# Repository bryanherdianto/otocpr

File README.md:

<h1 align="center">OtoCPR (Auto-CPR for Infants)</h1>

<p align="center">
  Adaptive infant mechanical chest compression system with dual-feedback control and live telemetry.
</p>

## Table of Contents

- [Overview](#overview)
- [Clinical Background and Problem Statement](#clinical-background-and-problem-statement)
- [System Architecture](#system-architecture)
  - [Dual-Feedback Control](#dual-feedback-control)
- [Hardware and PCB Design](#hardware-and-pcb-design)
  - [Custom PCB Details](#custom-pcb-details)
  - [3D Board View](#3d-board-view)
  - [Pin Mapping](#pin-mapping)
- [Firmware (ESP32)](#firmware-esp32)
  - [GPS Simulation](#gps-simulation)
  - [Build Environments](#build-environments)
- [Flutter Companion App](#flutter-companion-app)
- [Project Structure](#project-structure)
- [Quick Start](#quick-start)
  - [1. Firmware and Wokwi](#1-firmware-and-wokwi)
  - [2. Flutter App](#2-flutter-app)
- [Team](#team)

## Overview

OtoCPR is a portable mechanical chest compression device made for infants under 1 year old during CPR. It was developed at the Department of Electrical Engineering, Universitas Indonesia (FTUI), with pediatric intensive care specialists from FKUI-RSCM to reduce rescuer fatigue and keep compressions steady.

The system includes:

1. ESP32 motor control running on FreeRTOS.
2. Dual sensor feedback using a rotary encoder for depth and an HX711 load cell for force limits.
3. A custom 2-layer PCB with a 24V-to-5V buck regulator, level shifters, and motor driver wiring.
4. Wireless Bluetooth (BLE) and GPS data streamed to a Flutter app.

## Clinical Background and Problem Statement

Pediatric CPR guidelines from the American Heart Association (AHA) and European Resuscitation Council (ERC) recommend:

- Rate: 100 to 120 compressions per minute (CPM).
- Depth: about one-third of chest depth (roughly 3.5 to 4.0 cm).
- Recoil: full chest release between compressions.

<p align="center">
  
  <br />
  Figure 1: Adult mechanical CPR systems (left) compared with manual two-finger infant CPR (right).
</p>

Why OtoCPR is needed:

- Adult CPR machines (such as LUCAS 3) push 5.0 to 5.5 cm with over 300 N of force, which is unsafe for infants.
- Manual infant CPR causes hand fatigue within about 2 minutes, making depth and rate drop.
- Dedicated automated CPR devices for infants are rare, especially for ambulance transport and rural clinics.

## System Architecture

### Dual-Feedback Control

OtoCPR uses two sensors to keep compressions accurate and safe:

1. Depth control (Rotary Encoder):
   - A 600 PPR quadrature encoder (2400 counts per turn) tracks travel down to about 0.0033 mm per step.
   - A PID loop adjusts motor PWM output to hold the target stroke (3.5 to 4.0 cm) and speed (100 to 120 CPM).

2. Force limit (HX711 Load Cell):
   - A 24-bit load cell reads compression force continuously.
   - If force gets too high, the controller slows the motor and allows full recoil.

```mermaid
flowchart LR
    SP[AHA Target 100-120 CPM] --> PID[ESP32 PID]
    PID --> Driver[Motor Driver]
    Driver --> Actuator[DC Actuator]
    Actuator --> Chest[Infant Manikin]
    Actuator -. Depth .-> Enc[Rotary Encoder]
    Chest -. Force .-> LC[HX711 Load Cell]
    Enc -- Depth Feedback --> PID
    LC -- Force Limit --> PID
    PID -- BLE / Serial --> App[Flutter App]
```

## Hardware and PCB Design

The electronics sit on a custom 2-layer KiCad PCB to avoid loose breadboard wires and cut electrical noise.

### Custom PCB Details

<p align="center">
  
  <br />
  Figure 2: 2D KiCad board layout and specifications (DESPRO 2026 Kelompok 20).
</p>

| Item                | Value                            | Notes                                           |
| :------------------ | :------------------------------- | :---------------------------------------------- |
| Board Size          | 60.00 mm x 100.00 mm             | Compact size for portable housing               |
| Layers              | 2 copper layers (top and bottom) | 1 oz copper (0.035 mm)                          |
| Material            | FR4, 1.51 mm core                | Total thickness 1.60 mm                         |
| Min Track / Spacing | 0.200 mm / 0.200 mm              | Wider traces for motor power                    |
| Min Hole Size       | 0.400 mm                         | Plated through-holes                            |
| Power Converter     | XL4015E1 DC-DC buck              | Steps 24V battery down to 5V (5A peak)          |
| Level Shifter       | Dual BSS138 N-MOSFET             | Converts 5V encoder signals to 3.3V             |
| Protection          | 3A glass fuse and SS34 diodes    | Surge, reverse polarity, and flyback protection |

### 3D Board View

<p align="center">
  
  <br />
  Figure 3: 3D render of the assembled control board.
</p>

### Pin Mapping

| Part                 | Module Pin      | ESP32 Pin           | Notes                                |
| :------------------- | :-------------- | :------------------ | :----------------------------------- |
| Main Power           | Buck Output     | 5V / GND            | 5V rail from XL4015 converter        |
| Logic Reference      | 3.3V Rail       | 3V3                 | Reference for level shifter and MCU  |
| Rotary Encoder ChA   | Output A        | GPIO 32 (or GPIO 2) | Pulse interrupt via level shifter    |
| Rotary Encoder ChB   | Output B        | GPIO 33 (or GPIO 3) | Direction signal via level shifter   |
| HX711 Load Cell      | DT / SCK        | GPIO 19 / GPIO 18   | Weight sensor data and clock         |
| Motor Driver PWM     | IN1 / IN2       | GPIO 25 / GPIO 26   | 5 kHz, 8-bit PWM speed and direction |
| Driver Enable        | EN              | GPIO 27             | Motor enable (active HIGH)           |
| I2C Display          | SDA / SCL       | GPIO 21 / GPIO 22   | Status LCD (0x27 or 0x3C)            |
| NEO-6M GPS           | TX / RX         | GPIO 16 / GPIO 17   | Serial2 at 9600 baud                 |
| Buzzer / Stop Button | Buzzer / Switch | GPIO 8              | Emergency alarm and manual stop      |

## Firmware (ESP32)

Built with PlatformIO and C++, the firmware splits motor control and data sending across both ESP32 cores. See [Firmware/README.md](./Firmware/README.md) for full firmware instructions.

- Core 1 (Motor Control):
  - Counts encoder pulses using hardware interrupts.
  - Runs the PID loop every 10 ms (100 Hz) with deadband handling.
- Core 0 (Sensors and Data):
  - Reads the HX711 load cell and NEO-6M GPS.
  - Sends a 14-column CSV line every 200 ms (5 Hz) over Bluetooth (BLE) and USB Serial (115200 baud).

CSV format:

```text
Time(ms),Set_RPM,Actual_RPM,PWM,Raw_Counts,Freq_Hz,LoadCell,GPS_Fix,Latitude,Longitude,Satellites,Speed_kmh,Altitude_m,GPS_UTC
```

### GPS Simulation

To test GPS without a physical module or outdoor signal:

- A built-in GPS emulator generates NMEA data inside the ESP32.
- A custom Wokwi GPS chip (Firmware/chips/gps-neo6m.chip.c) adds live sliders for speed, heading, satellites, and signal strength.

### Build Environments

```bash
# Standard build for real hardware or Wokwi
pio run -e esp32doit-devkit-v1

# Built-in GPS software simulator
pio run -e esp32doit-devkit-v1-gps-sim -t upload

# Wireless Bluetooth (BLE) telemetry build
pio run -e esp32doit-devkit-v1-ble -t upload

# Desktop GPS tests
pio test -e native
```

## Flutter Companion App

The Flutter app runs on Android, iOS, Windows, macOS, and Linux:

- System Monitor: live gauges and charts for target vs actual rate, depth, PWM, and force.
- GPS Tracker: live unit location during transport.
- Edge AI Diagnostics: uses a Gemma model pipeline to flag anomalies, overheating risk, and compression consistency.
- Two Connection Modes:
  1. Bluetooth (BLE): connects wirelessly to OtoCPR Unit 01.
  2. Wokwi TCP: connects to the local simulator on 127.0.0.1:4000 (or 10.0.2.2:4000 on Android Emulator).

## Project Structure

```text
otocpr-main/
├── README.md                  Project overview
├── Hardware/                  Schematics, BOM, and datasheets
│   ├── BOM.md                 Parts list
│   ├── Datasheet/             Component datasheets
│   └── Schematic/             KiCad files
├── Firmware/                  PlatformIO ESP32 firmware
│   ├── platformio.ini         Build environments and libraries
│   ├── diagram.json           Wokwi circuit wiring
│   ├── wokwi.toml             Wokwi config
│   ├── log_serial.py          CSV logger script
│   ├── src/                   Firmware source code
│   ├── lib/                   GPS parser and helper code
│   └── chips/                 Custom Wokwi GPS chip
├── docs/                      Reports and figures
├── lib/                       Flutter app source code
│   ├── main.dart              App entry point
│   ├── models/                Telemetry data models
│   ├── screens/               App pages
│   ├── services/              BLE and Wokwi connection handlers
│   └── widgets/               Charts, gauges, and cards
└── assets/                    Images and icons
```

## Quick Start

### 1. Firmware and Wokwi

1. Install VS Code with the PlatformIO IDE and Wokwi for VS Code extensions.
2. Open the Firmware folder in VS Code.
3. Build the firmware:
   ```bash
   pio run -e esp32doit-devkit-v1
   ```
4. Open Firmware/diagram.json and click Start Simulation (opens local port 4000).

### 2. Flutter App

1. Install Flutter (3.0 or newer).
2. Install packages:
   ```bash
   flutter pub get
   ```
3. Run the app:
   ```bash
   flutter run -d macos
   flutter run -d windows
   flutter run -d android
   ```
4. In the Robotic System card, open the menu and select Connect Wokwi Simulator (:4000), or scan for OtoCPR Unit 01 over Bluetooth.

## Team

- Raditya Danendra - Project Lead, Control and Embedded System
- Bryan Herdianto - Flutter App and Telemetry Pipeline
- Daffa Sayra Firdaus - Sensor Instrumentation and Edge AI
- Fathih Rayyandra Firmansyah - Power Management and Electronics
- Lukas Sudibyo Putra Parulian - Mechanical Design and Actuation

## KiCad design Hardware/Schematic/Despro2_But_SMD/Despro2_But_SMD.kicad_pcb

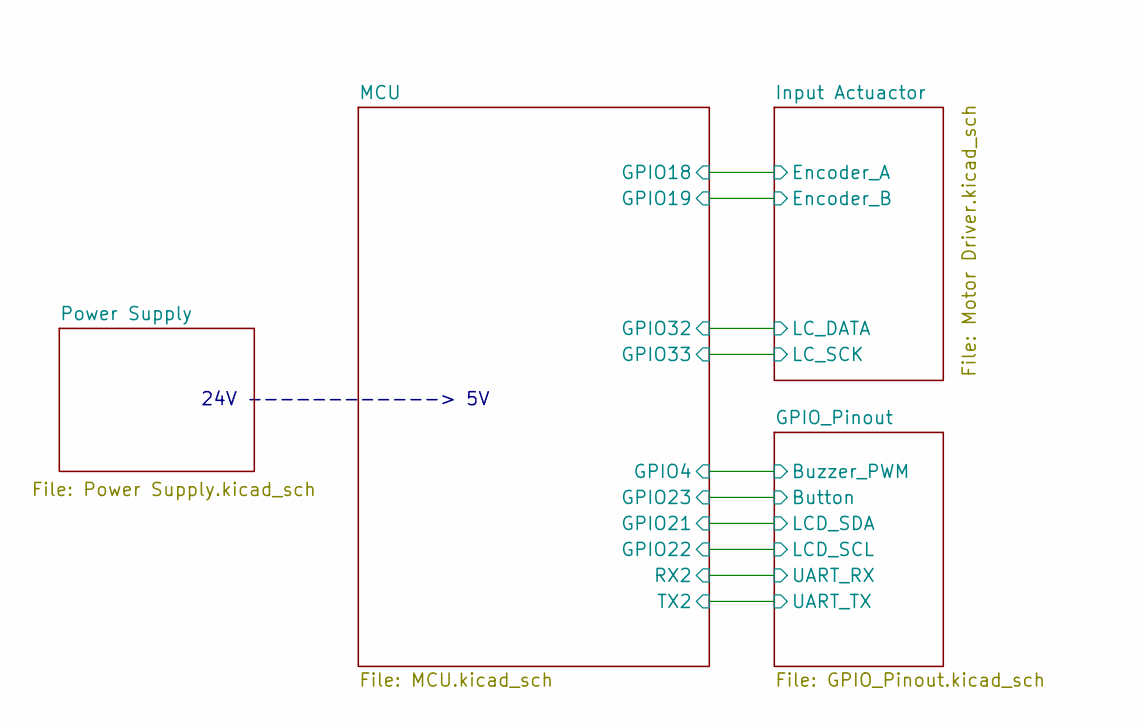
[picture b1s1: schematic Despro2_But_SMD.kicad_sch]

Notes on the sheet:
24V ------------> 5V

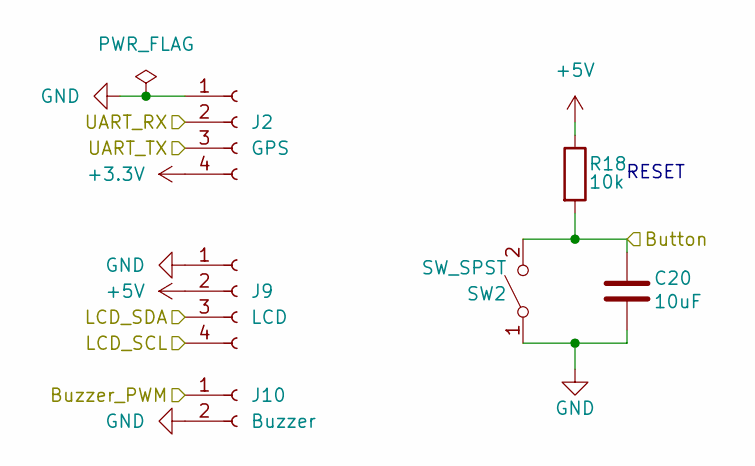
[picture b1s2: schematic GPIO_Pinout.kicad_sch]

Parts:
C20: 10uF; C_1206_3216Metric_Pad1.33x1.80mm_HandSolder; MANUFACTURER_PART_NUMBER GRM188D71A106KA73D
J2: GPS; Molex_KK-254_AE-6410-04A_1x04_P2.54mm_Vertical
J9: LCD; Molex_KK-254_AE-6410-04A_1x04_P2.54mm_Vertical
J10: Buzzer; Molex_KK-254_AE-6410-02A_1x02_P2.54mm_Vertical
R18: 10k; R_1206_3216Metric_Pad1.30x1.75mm_HandSolder; MANUFACTURER_PART_NUMBER RT0603FRE0710KL
SW2: SW_SPST; SW_PUSH_6mm; MANUFACTURER_PART_NUMBER TL1105F160QWITHSTRAIGHT

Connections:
+3.3V: J2.4; also elsewhere on the board
+5V: J9.2, R18.1; also elsewhere on the board
/MCU/GPIO4: J10.1; also elsewhere on the board
/MCU/GPIO21: J9.3; also elsewhere on the board
/MCU/GPIO22: J9.4; also elsewhere on the board
/MCU/GPIO23: C20.1, R18.2, SW2.2 (B); also elsewhere on the board
/MCU/RX2: J2.2; also elsewhere on the board
/MCU/TX2: J2.3; also elsewhere on the board
GND: C20.2, J2.1, J9.1, J10.2, SW2.1 (A); also elsewhere on the board

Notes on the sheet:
RESET

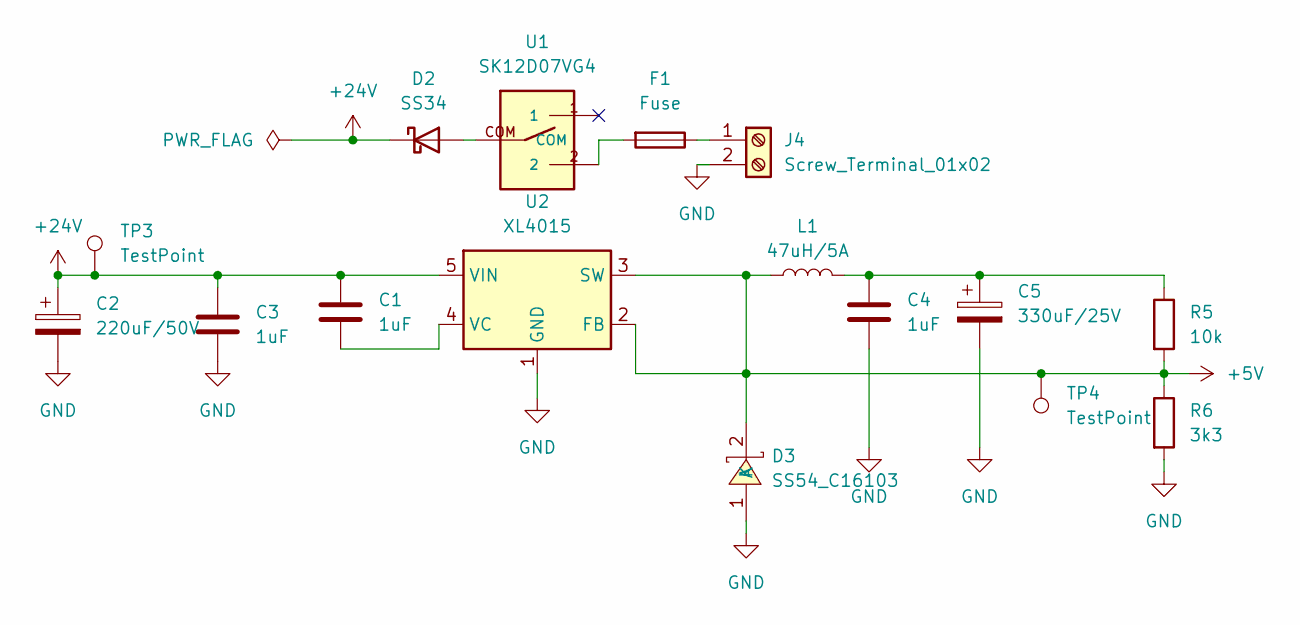
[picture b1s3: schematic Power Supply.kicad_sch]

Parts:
C1, C3, C4: 1uF; C_1206_3216Metric_Pad1.33x1.80mm_HandSolder
C2: 220uF/50V; CP_Radial_D10.0mm_P5.00mm
C5: 330uF/25V; CP_Radial_D8.0mm_P3.50mm
D2: SS34; D_SMA
D3: SS54_C16103; SMC_L7.1-W6.2-LS8.1-R-RD; MPN SS54C; LCSC Part C16103
F1: Fuse; Fuseholder_Littelfuse_Nano2_154x
J4: Screw_Terminal_01x02; TerminalBlock_Phoenix_PT-1,5-2-3.5-H_1x02_P3.50mm_Horizontal
L1: 47uH/5A; L_Sunlord_MWSA1206S-1R5
R5: 10k; R_1206_3216Metric_Pad1.30x1.75mm_HandSolder
R6: 3k3; R_1206_3216Metric_Pad1.30x1.75mm_HandSolder
TP3, TP4: TestPoint; PinHeader_1x01_P2.54mm_Vertical
U1: SK12D07VG4
U2: XL4015; TO-263-5_TabPin3

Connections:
+5V: D3.2 (K), L1.1, R5.2, R6.1, TP4.1 (1_1), U2.2 (FB), U2.3 (SW); also elsewhere on the board
+24V: C1.1, C2.1, C3.1, D2.1 (K), TP3.1 (1_1), U2.5 (VIN)
GND: C2.2, C3.2, C4.2, C5.2, D3.1 (A), J4.2, R6.2, U1.M1, U1.M2, U2.1 (GND); also elsewhere on the board
unnamed: C4.1, C5.1, L1.2, R5.1
unnamed: D2.2 (A), U1.COM
unnamed: F1.2, U1.2
unnamed: F1.1, J4.1
unnamed: C1.2, U2.4 (VC)

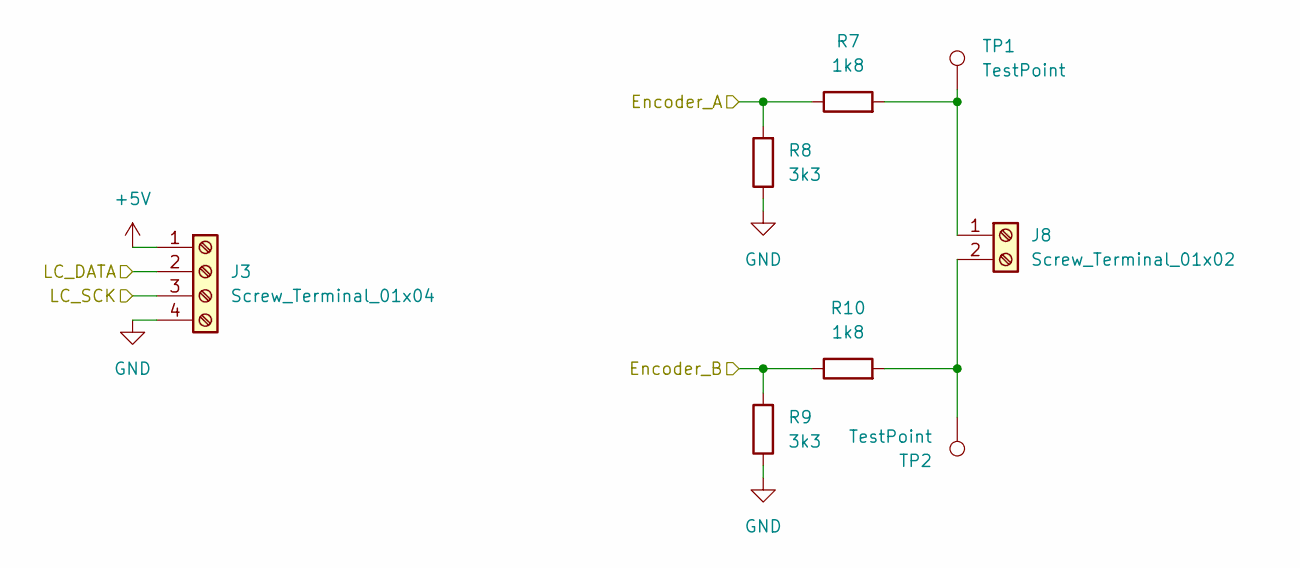
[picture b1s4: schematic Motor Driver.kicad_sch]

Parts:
J3: Screw_Terminal_01x04; TerminalBlock_Phoenix_PT-1,5-4-3.5-H_1x04_P3.50mm_Horizontal
J8: Screw_Terminal_01x02; TerminalBlock_Phoenix_PT-1,5-2-3.5-H_1x02_P3.50mm_Horizontal
R7, R10: 1k8; R_1206_3216Metric_Pad1.30x1.75mm_HandSolder
R8, R9: 3k3; R_1206_3216Metric_Pad1.30x1.75mm_HandSolder
TP1, TP2: TestPoint; PinHeader_1x01_P2.54mm_Vertical

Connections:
+5V: J3.1; also elsewhere on the board
/MCU/GPIO18: R7.1, R8.2; also elsewhere on the board
/MCU/GPIO19: R9.2, R10.1; also elsewhere on the board
/MCU/GPIO32: J3.2; also elsewhere on the board
/MCU/GPIO33: J3.3; also elsewhere on the board
GND: J3.4, R8.1, R9.1; also elsewhere on the board
unnamed: J8.1, R7.2, TP1.1 (1_1)
unnamed: J8.2, R10.2, TP2.1 (1_1)

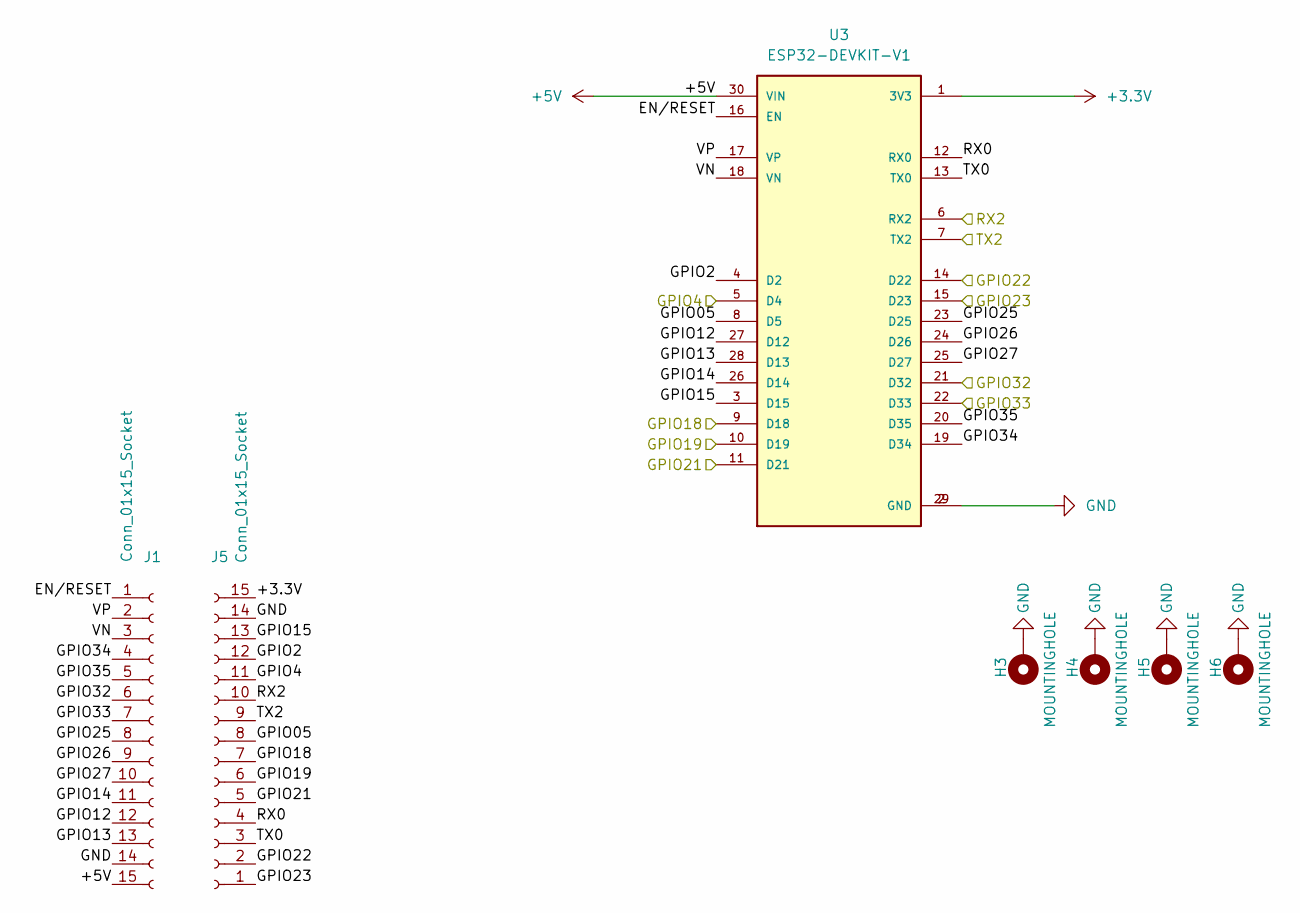
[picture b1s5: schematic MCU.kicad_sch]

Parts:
H3, H4, H5, H6: MOUNTINGHOLE; MountingHole_3.2mm_M3_Pad_Via
J1, J5: Conn_01x15_Socket; PinSocket_1x15_P2.54mm_Vertical
U3: ESP32-DEVKIT-V1; MODULE_ESP32_DEVKIT_V1; PARTREV N/A

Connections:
+3.3V: J5.15, U3.1 (3V3); also elsewhere on the board
+5V: J1.15, U3.30 (VIN); also elsewhere on the board
/MCU/EN/RESET: J1.1, U3.16 (EN)
/MCU/GPIO2: J5.12, U3.4 (D2)
/MCU/GPIO4: J5.11, U3.5 (D4); also elsewhere on the board
/MCU/GPIO05: J5.8, U3.8 (D5)
/MCU/GPIO12: J1.12, U3.27 (D12)
/MCU/GPIO13: J1.13, U3.28 (D13)
/MCU/GPIO14: J1.11, U3.26 (D14)
/MCU/GPIO15: J5.13, U3.3 (D15)
/MCU/GPIO18: J5.7, U3.9 (D18); also elsewhere on the board
/MCU/GPIO19: J5.6, U3.10 (D19); also elsewhere on the board
/MCU/GPIO21: J5.5, U3.11 (D21); also elsewhere on the board
/MCU/GPIO22: J5.2, U3.14 (D22); also elsewhere on the board
/MCU/GPIO23: J5.1, U3.15 (D23); also elsewhere on the board
/MCU/GPIO25: J1.8, U3.23 (D25)
/MCU/GPIO26: J1.9, U3.24 (D26)
/MCU/GPIO27: J1.10, U3.25 (D27)
/MCU/GPIO32: J1.6, U3.21 (D32); also elsewhere on the board
/MCU/GPIO33: J1.7, U3.22 (D33); also elsewhere on the board
/MCU/GPIO34: J1.4, U3.19 (D34)
/MCU/GPIO35: J1.5, U3.20 (D35)
/MCU/RX0: J5.4, U3.12 (RX0)
/MCU/RX2: J5.10, U3.6 (RX2); also elsewhere on the board
/MCU/TX0: J5.3, U3.13 (TX0)
/MCU/TX2: J5.9, U3.7 (TX2); also elsewhere on the board
/MCU/VN: J1.3, U3.18 (VN)
/MCU/VP: J1.2, U3.17 (VP)
GND: H3.1 (1_1), H4.1 (1_1), H5.1 (1_1), H6.1 (1_1), J1.14, J5.14, U3.2 (GND), U3.29 (GND); also elsewhere on the board

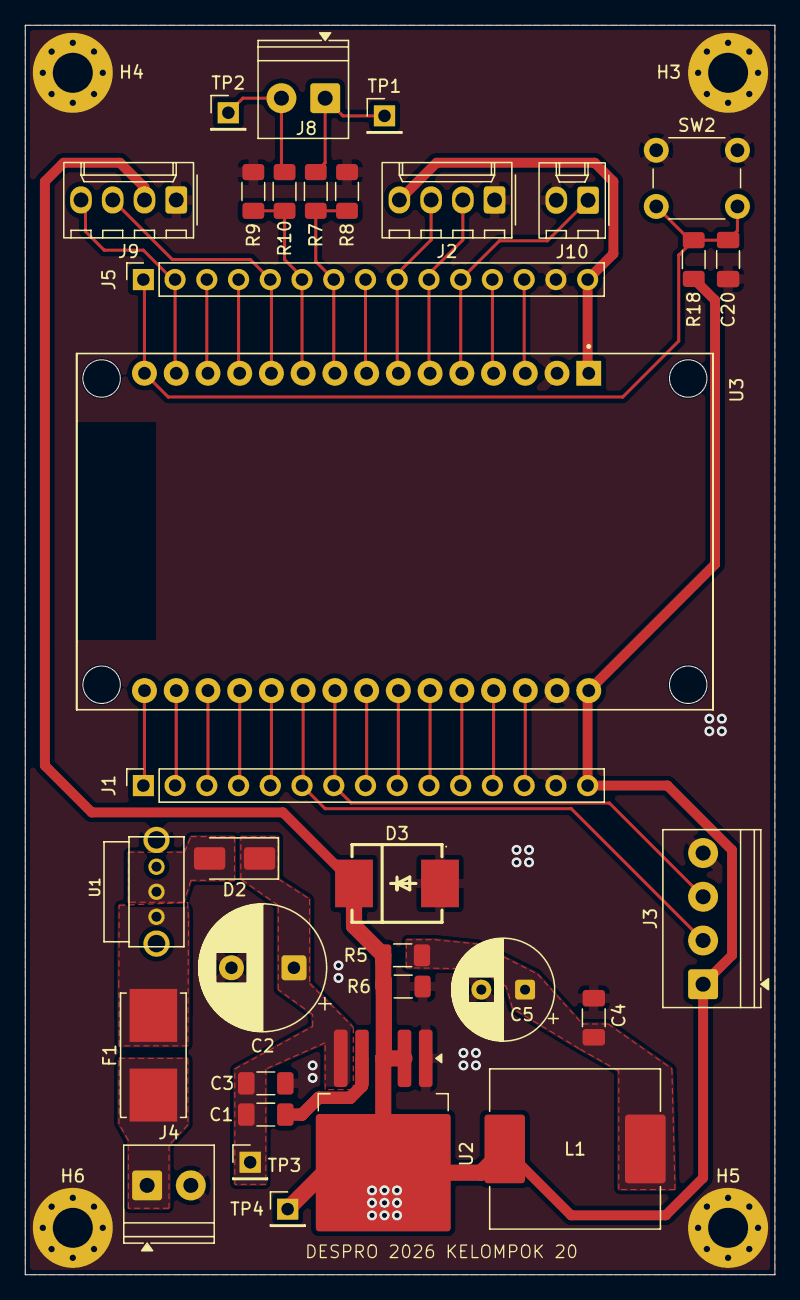
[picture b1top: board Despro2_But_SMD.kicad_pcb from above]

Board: 2 copper layers, 60.0 x 100.0 mm, 37 parts (0 on the bottom side), 37 nets.

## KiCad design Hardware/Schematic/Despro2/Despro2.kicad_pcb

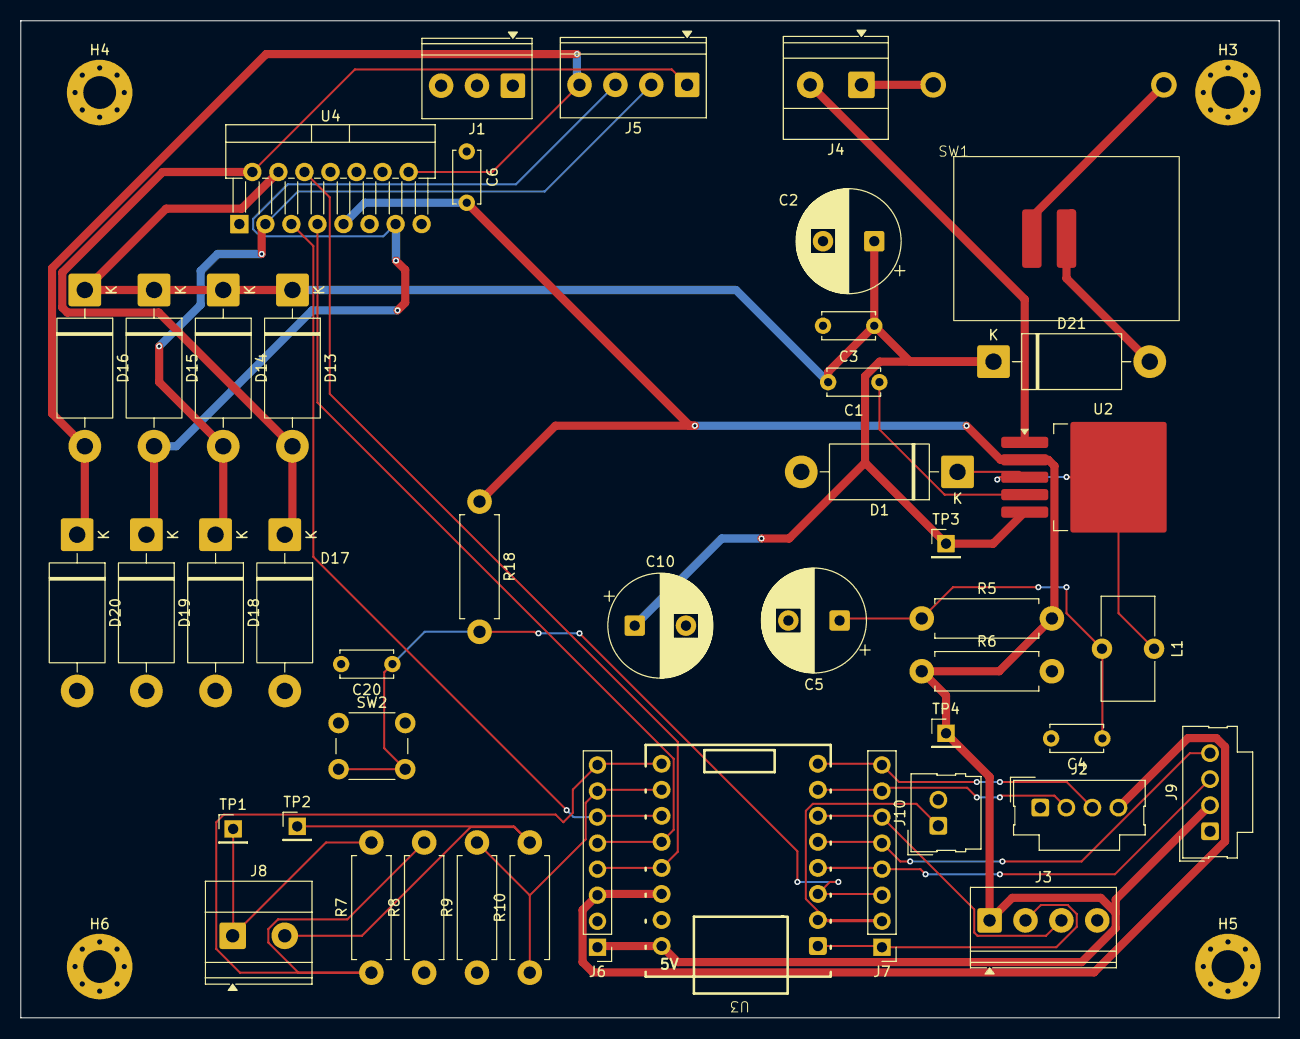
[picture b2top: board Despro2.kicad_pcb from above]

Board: 2 copper layers, 122.8 x 97.2 mm, 50 parts (0 on the bottom side), 32 nets.

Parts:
C1, C3, C4, C6: 1uF; C_Disc_D5.0mm_W2.5mm_P5.00mm
C2, C10: 220uF/50V; CP_Radial_D10.0mm_P5.00mm
C5: 330uF/25V; CP_Radial_D10.0mm_P5.00mm
C20: 10u; C_Disc_D5.0mm_W2.5mm_P5.00mm
D1: SR540; D_DO-201AD_P15.24mm_Horizontal
D13, D14, D15, D16, D17, D18, D19, D20, D21: 1N5822; D_DO-201AD_P15.24mm_Horizontal
F1: Fuse; Fuse-Holder-5x20
H3, H4, H5, H6: MOUNTINGHOLE; MountingHole_3.2mm_M3_Pad_Via
J1: Screw_Terminal_01x03; TerminalBlock_Phoenix_PT-1,5-3-3.5-H_1x03_P3.50mm_Horizontal
J2: GPS; Molex_SL_171971-0004_1x04_P2.54mm_Vertical
J3, J5: Screw_Terminal_01x04; TerminalBlock_Phoenix_PT-1,5-4-3.5-H_1x04_P3.50mm_Horizontal
J4: Screw_Terminal_01x02; TerminalBlock_Phoenix_MKDS-1,5-2_1x02_P5.00mm_Horizontal
J6, J7: Conn_01x08_Pin; PinHeader_1x08_P2.54mm_Vertical
J8: Screw_Terminal_01x02; TerminalBlock_Phoenix_MKDS-1,5-2-5.08_1x02_P5.08mm_Horizont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
J9: LCD; Molex_SL_171971-0004_1x04_P2.54mm_Vertical
J10: Buzzer; Molex_SL_171971-0002_1x02_P2.54mm_Vertical
L1: 47uH/5A; L_Toroid_Vertical_L10.0mm_W5.0mm_P5.08mm
R5, R18: 10k; R_Axial_DIN0411_L9.9mm_D3.6mm_P12.70mm_Horizontal
R6: 3300; R_Axial_DIN0411_L9.9mm_D3.6mm_P12.70mm_Horizontal
R7, R10: 1k8; R_Axial_DIN0411_L9.9mm_D3.6mm_P12.70mm_Horizontal
R8, R9: 3k3; R_Axial_DIN0411_L9.9mm_D3.6mm_P12.70mm_Horizontal
SW1: SW_SPST; Switch
SW2: SW_SPST; SW_PUSH_6mm
TP1, TP2, TP3, TP4: TestPoint; PinHeader_1x01_P2.54mm_Vertical
U2: XL4015; TO-263-5_TabPin3
U3: ESP32C3-SUPERMINI; ESP32-C3-SuperMini_THT.
U4: L298N; TO-220-15_P2.54x5.08mm_StaggerOdd_Lead4.58mm_Vertical

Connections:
+3.3V: J2.4, J6.3, U3.14 (3V3)
+5V: C6.2, J3.1, J6.1, J9.2, R5.2, R6.1, R18.1, TP4.1 (1_1), U2.2 (FB), U3.16 (5V), U4.9 (Vss)
+24V: C1.1, C2.1, C3.1, C10.1, D13.1 (K), D14.1 (K), D15.1 (K), D16.1 (K), D21.1 (K), TP3.1 (1_1), U2.5 (VIN), U4.4 (Vs)
/MCU/GPIO0: J6.8, R7.1, R8.2, U3.9 (GPIO0)
/MCU/GPIO1: J6.7, R9.2, R10.1, U3.10 (GPIO1)
/MCU/GPIO2: J6.6, U3.11 (GPIO2), U4.5 (IN1)
/MCU/GPIO3: J6.5, U3.12 (GPIO3), U4.7 (IN2)
/MCU/GPIO4: J6.4, U3.13 (GPIO4), U4.6 (EnA)
/MCU/GPIO5: J3.2, J7.1, U3.1 (GPIO5)
/MCU/GPIO6: J7.2, J10.1, U3.2 (GPIO6)
/MCU/GPIO7: C20.1, J7.3, R18.2, SW2.2 (B), U3.3 (GPIO7)
/MCU/GPIO8: J7.4, J9.3, U3.4 (GPIO8)
/MCU/GPIO9: J7.5, J9.4, U3.5 (GPIO9)
/MCU/GPIO10: J3.3, J7.6, U3.6 (GPIO10)
/MCU/GPIO20: J2.2, J7.7, U3.7 (GPIO20)
/MCU/GPIO21: J2.3, J7.8, U3.8 (GPIO21)
GND: C2.2, C3.2, C4.2, C5.2, C6.1, C10.2, C20.2, D1.2 (A), D17.2 (A), D18.2 (A), D19.2 (A), D20.2 (A), H3.1 (1_1), H4.1 (1_1), H5.1 (1_1), H6.1 (1_1), J2.1, J3.4, J4.2, J6.2, J9.1, J10.2, R6.2, R8.1, R9.1, SW2.1 (A), U2.1 (GND), U3.15 (GND), U4.1 (SENSE_A), U4.8 (GND), U4.15 (SENSE_B)
unnamed: C4.1, C5.1, L1.2, R5.1
unnamed: D1.1 (K), L1.1, U2.3 (SW)
unnamed: D13.2 (A), D17.1 (K), J5.1, U4.2 (OUT1)
unnamed: D14.2 (A), D18.1 (K), J5.2, U4.3 (OUT2)
unnamed: D15.2 (A), D19.1 (K), J5.3, U4.13 (OUT3)
unnamed: D16.2 (A), D20.1 (K), J5.4, U4.14 (OUT4)
unnamed: D21.2 (A), SW1.1 (A)
unnamed: J1.1, U4.11 (EnB)
unnamed: J1.2, U4.12 (IN4)
unnamed: J1.3, U4.10 (IN3)
unnamed: F1.1, J4.1
unnamed: J8.1, R7.2, TP1.1 (1_1)
unnamed: J8.2, R10.2, TP2.1 (1_1)
unnamed: F1.2, SW1.2 (B)
unnamed: C1.2, U2.4 (VC)
